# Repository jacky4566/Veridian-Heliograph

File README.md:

# Veridian-Heliograph
## What is it?
A hardy solar powered giver of GPS XYZ. Born from a need to always have a GPS device that can run for decades without any lithium batteries.
The Heliograph seeks to always provide a GPS Lat/Long position for the most severe travelers.
The whole device is cast in water clear epoxy, no ports, no holes, no batteries. Just a robust device that will provide a GPS position whenever outside.
A single M4 thread is provided for keychain or mounting on your favorite motorbike.

## Who wants it?
- Offshore Sailors
- Motorbikers
- Outdoorsmen
- Overlanders
- GNSS nerds

## Expected life
TBD

## Tech Features
- 2x 160mW solar panels
- TI nA Buck-Boost TPS63802
- 3.6V 70F Hybrid supercap
- UBlox Ultra low power M10 GPS processor
- STM32L432 MCU
- 3 Axis accelerometer with tap input, LIS3DH
- Sharp Sun readable Memory Display
- M4 screw thread for keychain or mounting

# Development and Details

## POWER SYSTEM
The power system comprises of 2 high efficiency solar panels at 120 degrees.  With this approach I hope the product design will always have access to some light to charge the super caps. Incoming power from the solar panels is feed through individual low drop shotcky diodes. With the diodes we loose ~200mV which is acceptable. 

The Supercaps are feed into Ti TPS63802 which provides buck-boost topography from the supercaps. Effectively allowing maximum use of the supercaps linear charge. 1.3 - 5.5V should be supported. Ti does also make an integrated BQ25570 MPPT with buck however I wanted to maximize the super caps voltage range.

VDD was selected at 3.0 volts as this was the minimum for the Sharp Memory LCD and the uBlox M10 GNSS chip. The M10 chip does also have a 1.8V version however we are still limited by the LCD. It might be possible to add a level converter however that quickly increases our BOM. The Buck-Boost seems like a good balance of low BOM and high efficiency.

## FIRMWARE
The firmware was written with the help of STM32CUBEIDE. The CubeIDE is pretty great for pre-generated code however some aspects can be hard to figure out for a novice. Since the BLE code could already be generated by the IDE most of my work was focused on the board level integration. Reading the sensors and putting that data into a nice GUI.
Firmware Features:
-	16MHz CPU speed coupled with 32.768kHz real time clock.
-	ADC 1Hz with DMA functionality to gather voltages. Supercap, temperature, and solar voltages.
-	SPI Display updating
-	GNSS processing using the Ublox PVT message. Less bytes to process compared to traditional NEMA messages. Super-e ultra low power tracking is set along side a software standby.
-	Accelerometer processing and Tap inputs

Some programming challenges I faced with my fight against CubeIDE:
-	Setting up the ADC DMA with proper callbacks. Some of the HAL calls need to be just right for the desired callbacks.
-	Learing about the SHARP display strange packet formatting. Data needs to be send as LSB.

## Housing
The Heliograph is essential without a housing. A basic model was 3D printed, then a reverse mold was made in rubber so the PCB and solar panels could be placed in a cavity and cast. Further development to come here.

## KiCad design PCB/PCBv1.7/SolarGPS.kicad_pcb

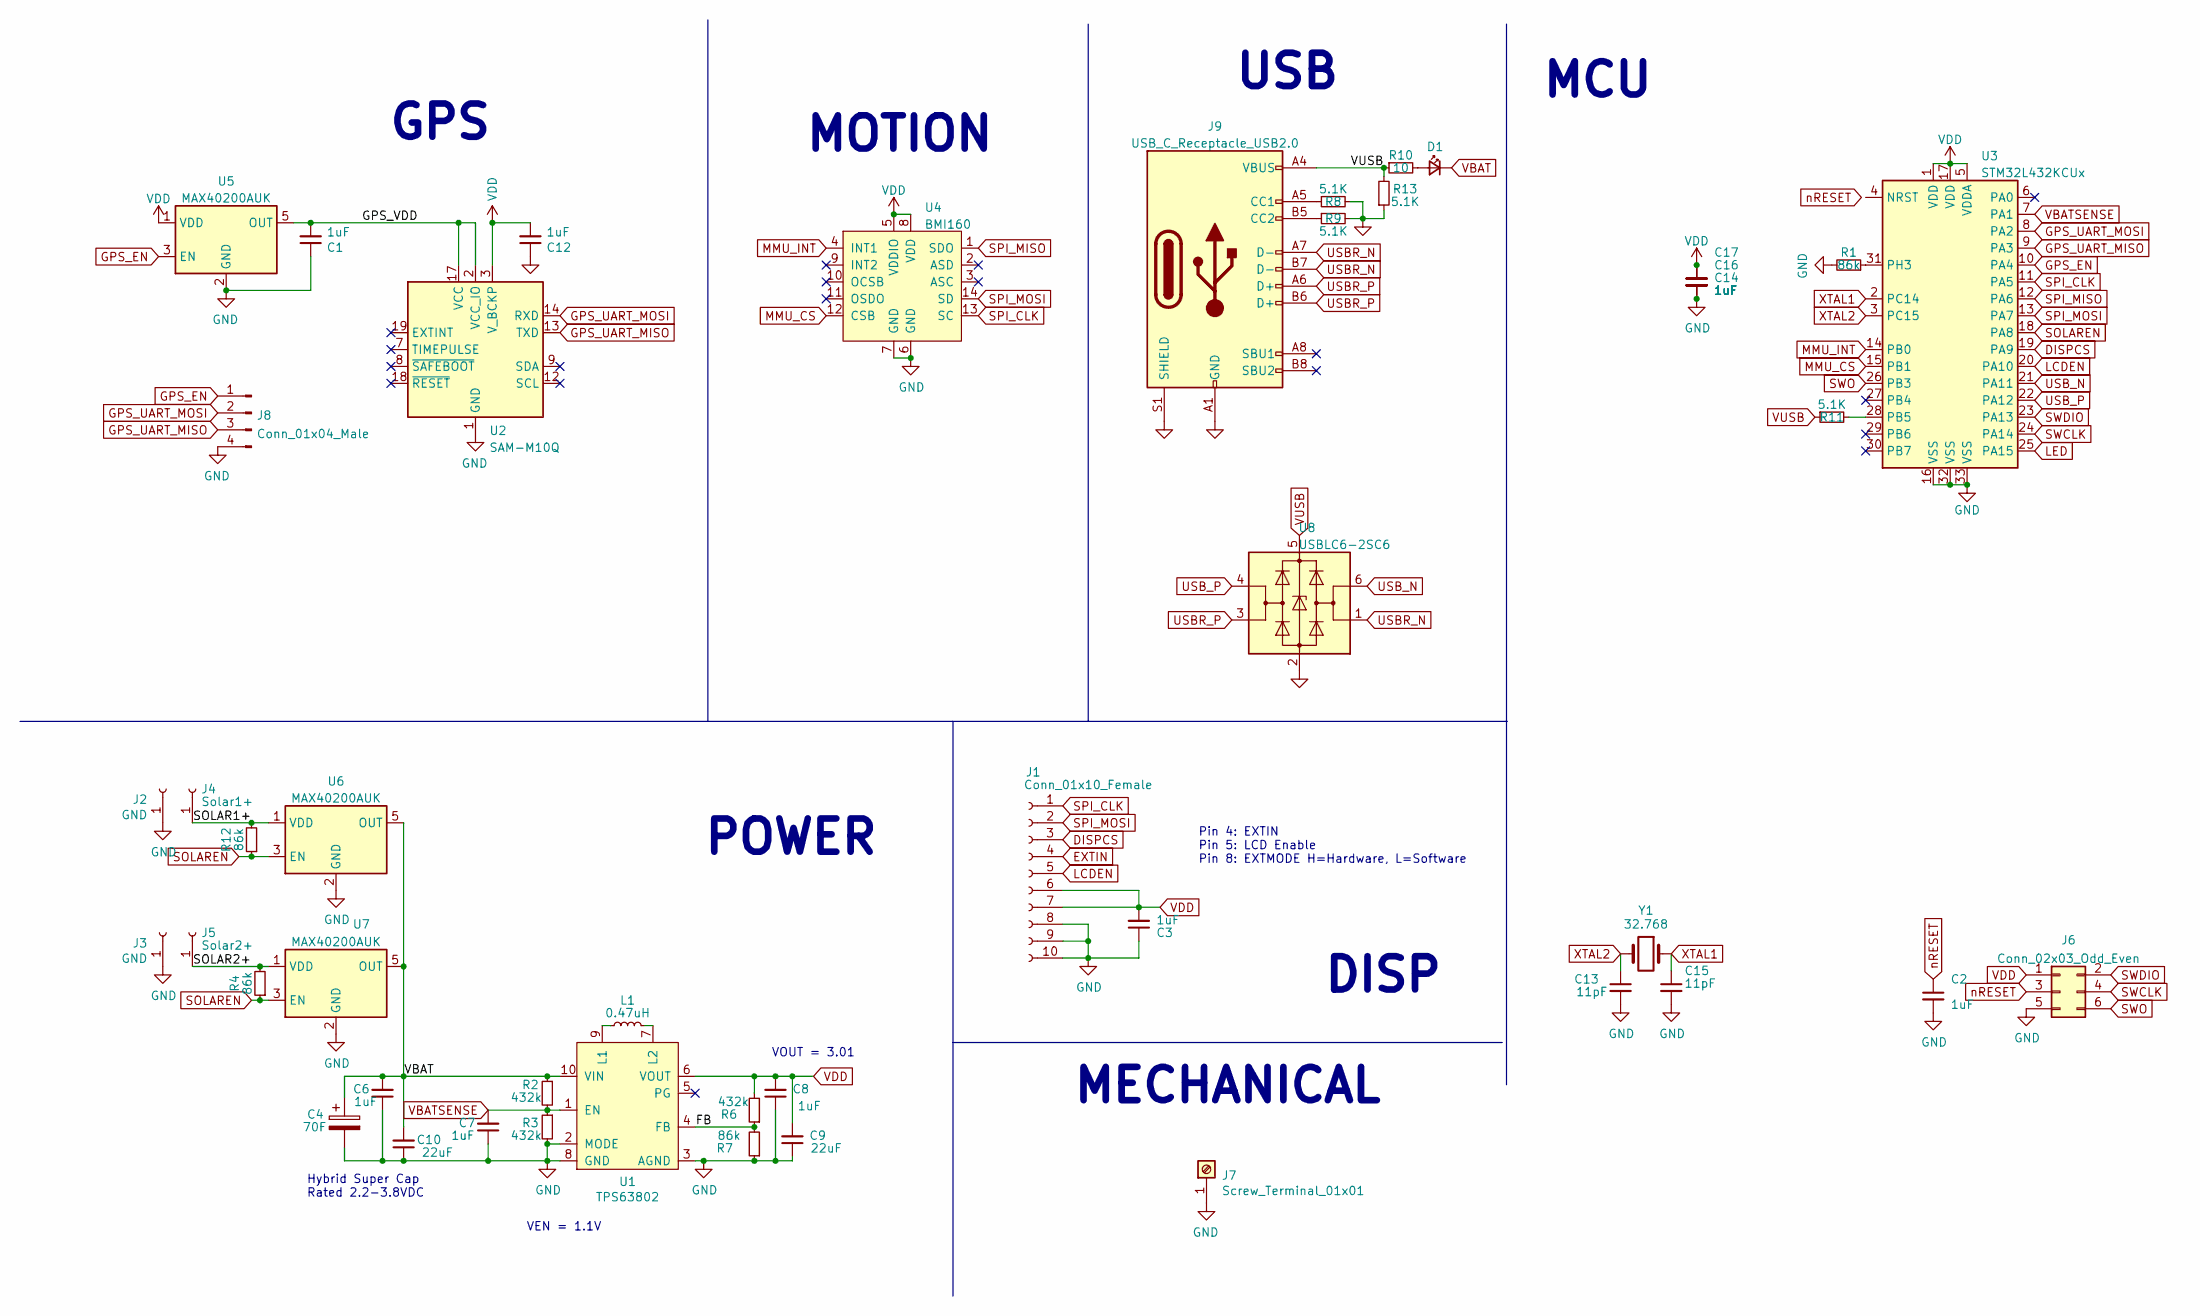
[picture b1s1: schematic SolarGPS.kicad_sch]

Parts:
C1, C2, C3, C6, C7, C8, C12, C14, C16, C17: 1uF; C_0603_1608Metric
C4: 70F; TPLC3R8-25MR8X20; Part TPLC3R8-25MR8X20
C9, C10: 22uF; C_1206_3216Metric
C13, C15: 11pF; C_0603_1608Metric
D1: LED_Small; D_0805_2012Metric
J1: Conn_01x10_Female; LS013B7DH03
J2, J3: GND; PinHeader_1x01_P2.54mm_Vertical
J4: Solar1+; PinHeader_1x01_P2.54mm_Vertical
J5: Solar2+; PinHeader_1x01_P2.54mm_Vertical
J6: Conn_02x03_Odd_Even; Tag-Connect_TC2030-IDC-NL_2x03_P1.27mm_Vertical
J7: Screw_Terminal_01x01; M4_RA_7792; Part 7792
J8: Conn_01x04_Male; PinSocket_1x04_P2.54mm_Vertical
J9: USB_C_Receptacle_USB2.0; USB_TYPE_C_PCB
L1: 0.47uH; L_0805_2012Metric_Pad1.15x1.40mm_HandSolder; Part DFE201612E
R1, R4, R7, R12: 86k; R_0603_1608Metric
R2, R3, R6: 432k; R_0603_1608Metric
R8, R9, R11, R13: 5.1K; R_0603_1608Metric
R10: 10; R_0805_2012Metric
U1: TPS63802; VREG_TPS63802DLAR
U2: SAM-M10Q; ublox_SAM-M8Q
U3: STM32L432KCUx; QFN-32-1EP_5x5mm_P0.5mm_EP3.45x3.45mm
U4: BMI160; MPN BMI160; Digi-Key_PN 828-1057-1-ND
U5, U6, U7: MAX40200AUK; SOT-23-5
U8: USBLC6-2SC6; SOT-23-6
Y1: 32.768; Crystal_SMD_3215-2Pin_3.2x1.5mm; Part SC32S-7PF20PPM

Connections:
/FB: R6.1, R7.2, U1.4 (FB)
/GPS_VDD: C1.2, U2.2 (VCC_IO), U2.17 (VCC), U5.5 (OUT)
/SOLAR1+: J4.1, R12.2, U6.1 (VDD)
/SOLAR2+: J5.1, R4.2, U7.1 (VDD)
DISPCS: J1.3, U3.19 (PA9)
EXTIN: J1.4
GND: C1.1, C2.2, C3.1, C4.2, C6.1, C7.1, C8.1, C9.1, C10.1, C12.1, C13.2, C14.2, C15.2, C16.2, C17.2, J1.8, J1.9, J1.10, J2.1, J3.1, J6.5, J7.1, J8.4, J9.A1 (GND), J9.A12 (GND), J9.B1 (GND), J9.B12 (GND), J9.S1 (SHIELD), R1.2, R3.2, R7.1, R8.2, R9.2, R13.1, U1.2 (MODE), U1.3 (AGND), U1.8 (GND), U2.1 (GND), U2.4 (GND), U2.5 (GND), U2.6 (GND), U2.10 (GND), U2.11 (GND), U2.15 (GND), U2.16 (GND), U2.20 (GND), U3.16 (VSS), U3.32 (VSS), U3.33 (VSS), U4.6 (GND), U4.7 (GND), U5.2 (GND), U6.2 (GND), U7.2 (GND), U8.2 (GND)
GPS_EN: J8.1, U3.10 (PA4), U5.3 (EN)
GPS_UART_MISO: J8.3, U2.13 (TXD), U3.9 (PA3)
GPS_UART_MOSI: J8.2, U2.14 (RXD), U3.8 (PA2)
LCDEN: J1.5, U3.20 (PA10)
LED: U3.25 (PA15)
MMU_CS: U3.15 (PB1), U4.12 (CSB)
MMU_INT: U3.14 (PB0), U4.4 (INT1)
unnamed: D1.2 (A), R10.2
unnamed: J9.A5 (CC1), R8.1
unnamed: J9.B5 (CC2), R9.1
unnamed: L1.1, U1.9 (L1)
unnamed: L1.2, U1.7 (L2)
unnamed: R1.1, U3.31 (PH3)
unnamed: R11.2, U3.28 (PB5)
SOLAREN: R4.1, R12.1, U3.18 (PA8), U6.3 (EN), U7.3 (EN)
SPI_CLK: J1.1, U3.11 (PA5), U4.13 (SC)
SPI_MISO: U3.12 (PA6), U4.1 (SDO)
SPI_MOSI: J1.2, U3.13 (PA7), U4.14 (SD)
SWCLK: J6.4, U3.24 (PA14)
SWDIO: J6.2, U3.23 (PA13)
SWO: J6.6, U3.26 (PB3)
USBR_N: J9.A7 (D-), J9.B7 (D-), U8.1 (I/O1)
USBR_P: J9.A6 (D+), J9.B6 (D+), U8.3 (I/O2)
USB_N: U3.21 (PA11), U8.6 (I/O1)
USB_P: U3.22 (PA12), U8.4 (I/O2)
VBAT: C4.1, C6.2, C10.2, D1.1 (K), R2.1, U1.10 (VIN), U6.5 (OUT), U7.5 (OUT)
VBATSENSE: C7.2, R2.2, R3.1, U1.1 (EN), U3.7 (PA1)
VDD: C3.2, C8.2, C9.2, C12.2, C14.1, C16.1, C17.1, J1.6, J1.7, J6.1, R6.2, U1.6 (VOUT), U2.3 (V_BCKP), U3.1 (VDD), U3.5 (VDDA), U3.17 (VDD), U4.5 (VDDIO), U4.8 (VDD), U5.1 (VDD)
VUSB: J9.A4 (VBUS), J9.A9 (VBUS), J9.B4 (VBUS), J9.B9 (VBUS), R10.1, R11.1, R13.2, U8.5 (VBUS)
XTAL1: C15.1, U3.2 (PC14), Y1.1
XTAL2: C13.1, U3.3 (PC15), Y1.2
nRESET: C2.1, J6.3

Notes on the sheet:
GPS
USB
MCU
Pin 4: EXTIN Pin 5: LCD Enable Pin 8: EXTMODE H=Hardware, L=Software
DISP
Hybrid Super Cap Rated 2.2-3.8VDC
VEN = 1.1V
POWER
VOUT = 3.01
MECHANICAL
MOTION

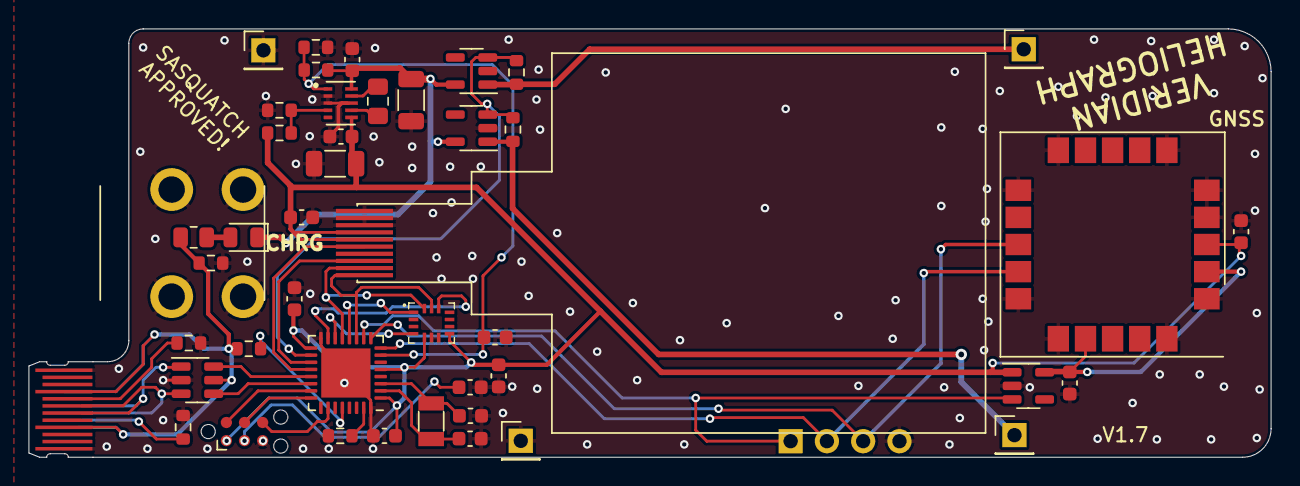
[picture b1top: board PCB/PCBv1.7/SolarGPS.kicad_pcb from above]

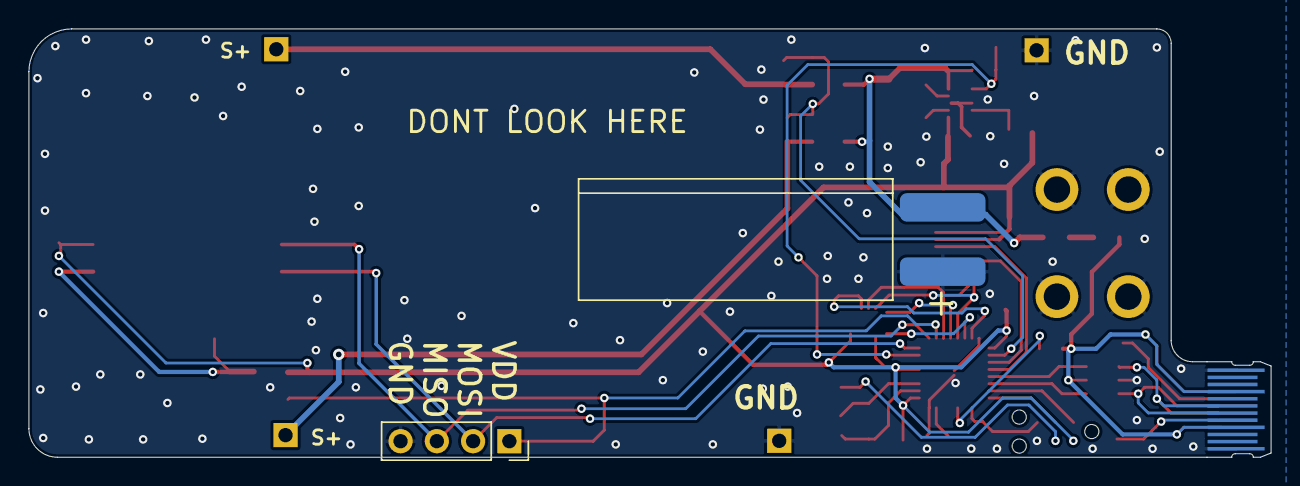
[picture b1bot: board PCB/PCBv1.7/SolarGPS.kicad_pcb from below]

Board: 2 copper layers, 87.0 x 30.0 mm, 47 parts (2 on the bottom side), 37 nets.

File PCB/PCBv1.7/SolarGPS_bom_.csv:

Component,Description,Part,References,Value,Footprint,Quantity Per PCB,Datasheet,Manufacture,Category,DK_Datasheet_Link,DK_Detail_Page,Digi-Key_PN,Family,MPN,Manufacturer,Status
1,"Unpolarized capacitor, small symbol",C_Small,C13 C15,11pF,C_0603_1608Metric,2,~,,,,,,,,,
2,"Unpolarized capacitor, small symbol",C_Small,C1 C2 C3 C6 C7 C8 C12 C14 C16 C17,1uF,C_0603_1608Metric,10,~,,,,,,,,,
3,"Unpolarized capacitor, small symbol",C_Small,C9 C10,22uF,C_1206_3216Metric,2,~,,,,,,,,,
4,Polarized capacitor,C_Polarized,C4,70F,TPLC3R8-25MR8X20,1,~,,,,,,,,,
5,"Light emitting diode, small symbol",LED_Small,D1,LED_Small,D_0805_2012Metric,1,~,,,,,,,,,
6,"Generic connector, single row, 01x04, script generated (kicad-library-utils/schlib/autogen/connector/)",Conn_01x04_Male,J8,Conn_01x04_Male,PinSocket_1x04_P2.54mm_Vertical,1,~,,,,,,,,,
7,"Generic connector, single row, 01x10, script generated (kicad-library-utils/schlib/autogen/connector/)",Conn_01x10_Female,J1,Conn_01x10_Female,LS013B7DH03,1,~,,,,,,,,,
8,"Generic connector, double row, 02x03, odd/even pin numbering scheme (row 1 odd numbers, row 2 even numbers), script generated (kicad-library-utils/schlib/autogen/connector/)",Conn_02x03_Odd_Even,J6,Conn_02x03_Odd_Even,Tag-Connect_TC2030-IDC-NL_2x03_P1.27mm_Vertical,1,~,,,,,,,,,
9,"Generic connector, single row, 01x01, script generated (kicad-library-utils/schlib/autogen/connector/)",Conn_01x01_Female,J2 J3 J4 J5,GND,PinHeader_1x01_P2.54mm_Vertical,4,~,,,,,,,,,
10,"Generic screw terminal, single row, 01x01, script generated (kicad-library-utils/schlib/autogen/connector/)",Screw_Terminal_01x01,J7,Screw_Terminal_01x01,M4_RA_7792,1,~,Keystone Electronics,,,,,,,,
11,USB 2.0-only Type-C Receptacle connector,USB_C_Receptacle_USB2.0,J9,USB_C_Receptacle_USB2.0,USB_TYPE_C_PCB,1,https://www.usb.org/sites/default/files/documents/usb_type-c.zip,,,,,,,,,
12,"Inductor, small symbol",L_Small,L1,0.47uH,L_0805_2012Metric_Pad1.15x1.40mm_HandSolder,1,~,,,,,,,,,
13,"Resistor, small symbol",R_Small,R10,10,R_0805_2012Metric,1,~,,,,,,,,,
14,"Resistor, small symbol",R_Small,R8 R9 R11 R13,5.1K,R_0603_1608Metric,4,~,,,,,,,,,
15,"Resistor, small symbol",R_Small,R1 R4 R7 R12,86.6k,R_0603_1608Metric,4,~,,,,,,,,,
16,"Resistor, small symbol",R_Small,R2 R3 R6,432k,R_0603_1608Metric,3,~,,,,,,,,,
17,IMU ACCEL/GYRO I2C/SPI 14LGA,BMI160,U4,BMI160,BMI160,1,https://ae-bst.resource.bosch.com/media/_tech/media/datashee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,,"Sensors, Transducers",https://ae-bst.resource.bosch.com/media/_tech/media/datashee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,/product-detail/en/bosch-sensortec/BMI160/828-1057-1-ND/6136308,828-1057-1-ND,Motion Sensors - IMUs (Inertial Measurement Units),BMI160,Bosch Sensortec,Active
18,"Ideal Diode, Ultra-Low Voltage Drop, 1.5-5.5V, 1A, SOT-23-5",MAX40200AUK,U5 U6 U7,MAX40200AUK,SOT-23-5,3,https://datasheets.maximintegrated.com/en/ds/MAX40200.pdf,,,,,,,,,
19,GPS ublox M8 variant,SAM-M8Q,U2,SAM-M10Q,ublox_SAM-M8Q,1,https://www.u-blox.com/sites/default/files/SAM-M8Q_DataSheet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,,,,,,,,,
20,"ARM Cortex-M4 MCU, 256KB flash, 64KB RAM, 80MHz, 1.71-3.6V, 26 GPIO, UFQFPN-32",STM32L432KCUx,U3,STM32L432KCUx,QFN-32-1EP_5x5mm_P0.5mm_EP3.45x3.45mm,1,http://www.st.com/st-web-ui/static/active/en/resource/techni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,,,,,,,,,
21,,TPS63802-VeridianDesigns,U1,TPS63802,VREG_TPS63802DLAR,1,,,,,,,,,,
22,"Very low capacitance ESD protection diode, 2 data-line, SOT-23-6",USBLC6-2SC6,U8,USBLC6-2SC6,SOT-23-6,1,https://www.st.com/resource/en/datasheet/usblc6-2.pdf,,,,,,,,,
23,Two pin crystal,Crystal,Y1,32.768,Crystal_SMD_3215-2Pin_3.2x1.5mm,1,~,,,,,,,,,





Component Groups:,23
Component Count:,47
Fitted Components:,47
Number of PCBs:,1
Total components:,47
Schematic Version:,
Schematic Date:,
PCB Variant:,default
BoM Date:,27-Apr-23 3:35:01 PM
Schematic Source:,SolarGPS.kicad_sch
KiCad Version:,Eeschema (6.0.10)

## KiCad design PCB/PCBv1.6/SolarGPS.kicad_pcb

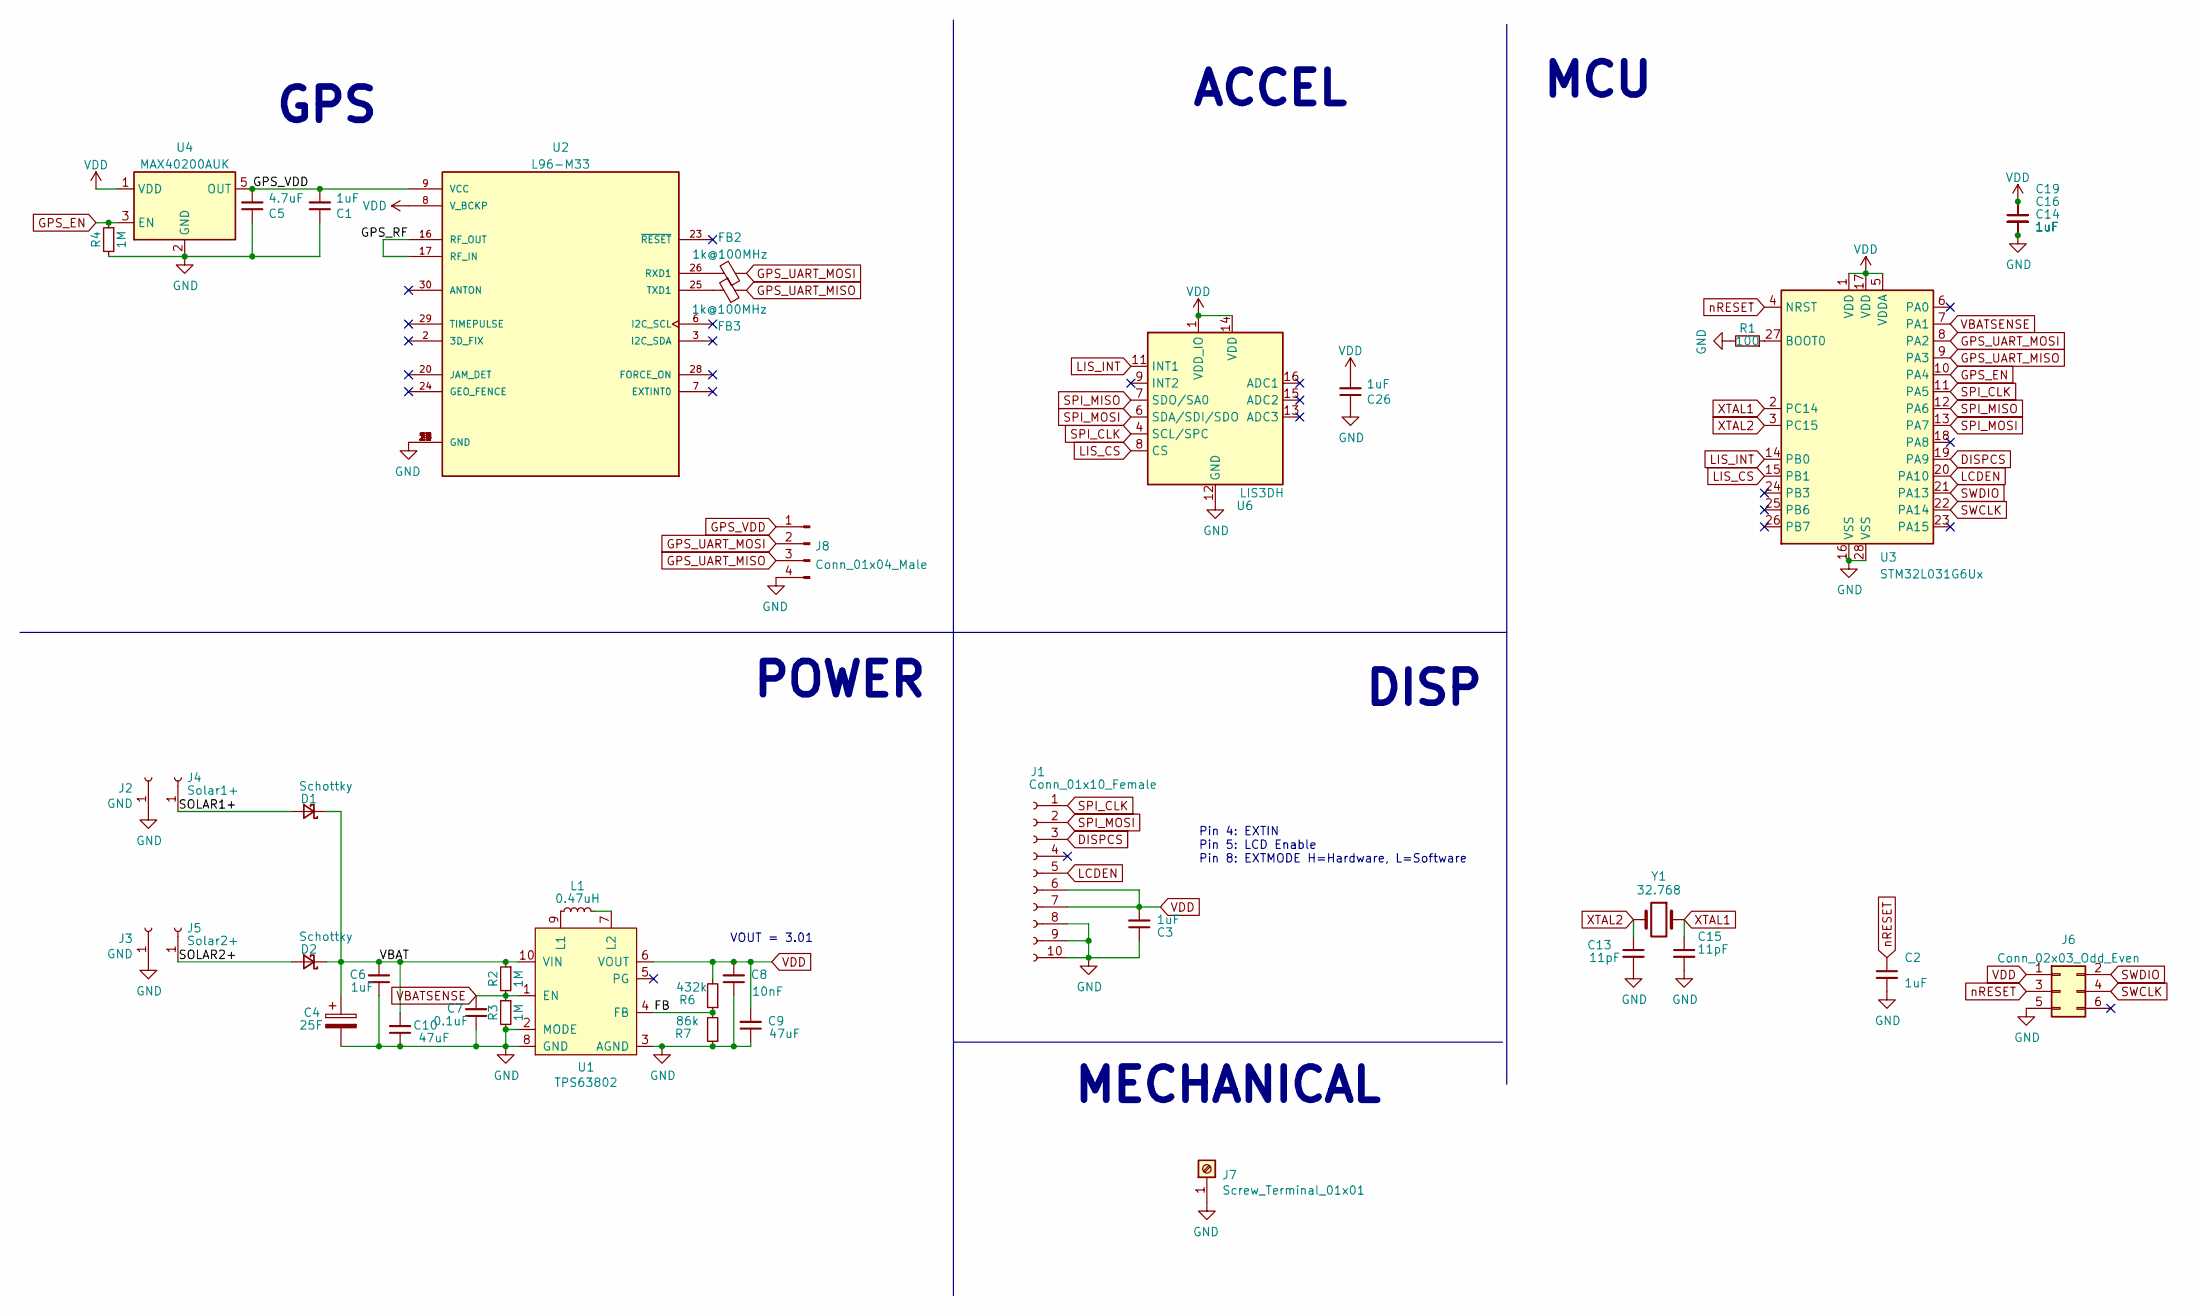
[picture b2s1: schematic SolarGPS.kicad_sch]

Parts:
C1, C2, C3, C6, C14, C16, C19, C26: 1uF; C_0603_1608Metric
C4: 25F; TPLC3R8-25MR8X20; Part TPLC3R8-25MR8X20
C5: 4.7uF; C_0805_2012Metric
C7: 0.1uF; C_0603_1608Metric
C8: 10nF; C_0603_1608Metric
C9, C10: 47uF; C_1206_3216Metric
C13, C15: 11pF; C_0603_1608Metric
D1, D2: Schottky; D_SOD-323_HandSoldering; Part B0530WS
FB2, FB3: 1k@100MHz; R_0603_1608Metric
J1: Conn_01x10_Female; LS013B7DH03
J2, J3: GND; PinHeader_1x01_P2.54mm_Vertical
J4: Solar1+; PinHeader_1x01_P2.54mm_Vertical
J5: Solar2+; PinHeader_1x01_P2.54mm_Vertical
J6: Conn_02x03_Odd_Even; Tag-Connect_TC2030-IDC-NL_2x03_P1.27mm_Vertical
J7: Screw_Terminal_01x01; M4_RA_7792; Part 7792
J8: Conn_01x04_Male; PinSocket_1x04_P2.54mm_Vertical
L1: 0.47uH; L_0805_2012Metric_Pad1.05x1.20mm_HandSolder; Part DFE201612E
R1: 100; R_0603_1608Metric
R2, R3, R4: 1M; R_0603_1608Metric
R6: 432k; R_0603_1608Metric
R7: 86k; R_0603_1608Metric
U1: TPS63802; VREG_TPS63802DLAR
U2: L96-M33; XCVR_L96-M33
U3: STM32L031G6Ux; QFN-28_4x4mm_P0.5mm
U4: MAX40200AUK; SOT-23-5
U6: LIS3DH; LGA-16_3x3mm_P0.5mm_LayoutBorder3x5y
Y1: 32.768; Crystal_SMD_3215-2Pin_3.2x1.5mm; Part SC32S-7PF20PPM

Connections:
/FB: R6.1, R7.2, U1.4 (FB)
/GPS_RF: U2.16 (RF_OUT), U2.17 (RF_IN)
/SOLAR1+: D1.2 (A), J4.1
/SOLAR2+: D2.2 (A), J5.1
/VBAT: C4.1, C6.2, C10.2, D1.1 (K), D2.1 (K), R2.1, U1.10 (VIN)
DISPCS: J1.3, U3.19 (PA9)
GND: C1.1, C2.2, C3.1, C4.2, C5.1, C6.1, C7.1, C8.1, C9.1, C10.1, C13.2, C14.2, C15.2, C16.2, C19.2, C26.1, J1.8, J1.9, J1.10, J2.1, J3.1, J6.5, J7.1, J8.4, R1.2, R3.2, R4.2, R7.1, U1.2 (MODE), U1.3 (AGND), U1.8 (GND), U2.4 (GND), U2.5 (GND), U2.10 (GND), U2.11 (GND), U2.12 (GND), U2.13 (GND), U2.14 (GND), U2.15 (GND), U2.18 (GND), U2.19 (GND), U2.21 (GND), U2.22 (GND), U2.27 (GND), U2.31 (GND), U3.16 (VSS), U3.28 (VSS), U4.2 (GND), U6.5 (GND), U6.10 (GND), U6.12 (GND)
GPS_EN: R4.1, U3.10 (PA4), U4.3 (EN)
GPS_UART_MISO: FB3.2, J8.3, U3.9 (PA3)
GPS_UART_MOSI: FB2.1, J8.2, U3.8 (PA2)
GPS_VDD: C1.2, C5.2, J8.1, U2.9 (VCC), U4.5 (OUT)
LCDEN: J1.5, U3.20 (PA10)
LIS_CS: U3.15 (PB1), U6.8 (CS)
LIS_INT: U3.14 (PB0), U6.11 (INT1)
unnamed: FB2.2, U2.26 (RXD1)
unnamed: FB3.1, U2.25 (TXD1)
unnamed: L1.1, U1.9 (L1)
unnamed: L1.2, U1.7 (L2)
unnamed: R1.1, U3.27 (BOOT0)
SPI_CLK: J1.1, U3.11 (PA5), U6.4 (SCL/SPC)
SPI_MISO: U3.12 (PA6), U6.7 (SDO/SA0)
SPI_MOSI: J1.2, U3.13 (PA7), U6.6 (SDA/SDI/SDO)
SWCLK: J6.4, U3.22 (PA14)
SWDIO: J6.2, U3.21 (PA13)
VBATSENSE: C7.2, R2.2, R3.1, U1.1 (EN), U3.7 (PA1)
VDD: C3.2, C8.2, C9.2, C14.1, C16.1, C19.1, C26.2, J1.6, J1.7, J6.1, R6.2, U1.6 (VOUT), U2.8 (V_BCKP), U3.1 (VDD), U3.5 (VDDA), U3.17 (VDD), U4.1 (VDD), U6.1 (VDD_IO), U6.14 (VDD)
XTAL1: C15.1, U3.2 (PC14), Y1.1
XTAL2: C13.1, U3.3 (PC15), Y1.2
nRESET: C2.1, J6.3, U3.4 (NRST)

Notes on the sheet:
GPS
MCU
ACCEL
Pin 4: EXTIN Pin 5: LCD Enable Pin 8: EXTMODE H=Hardware, L=Software
DISP
POWER
VOUT = 3.01
MECHANICAL

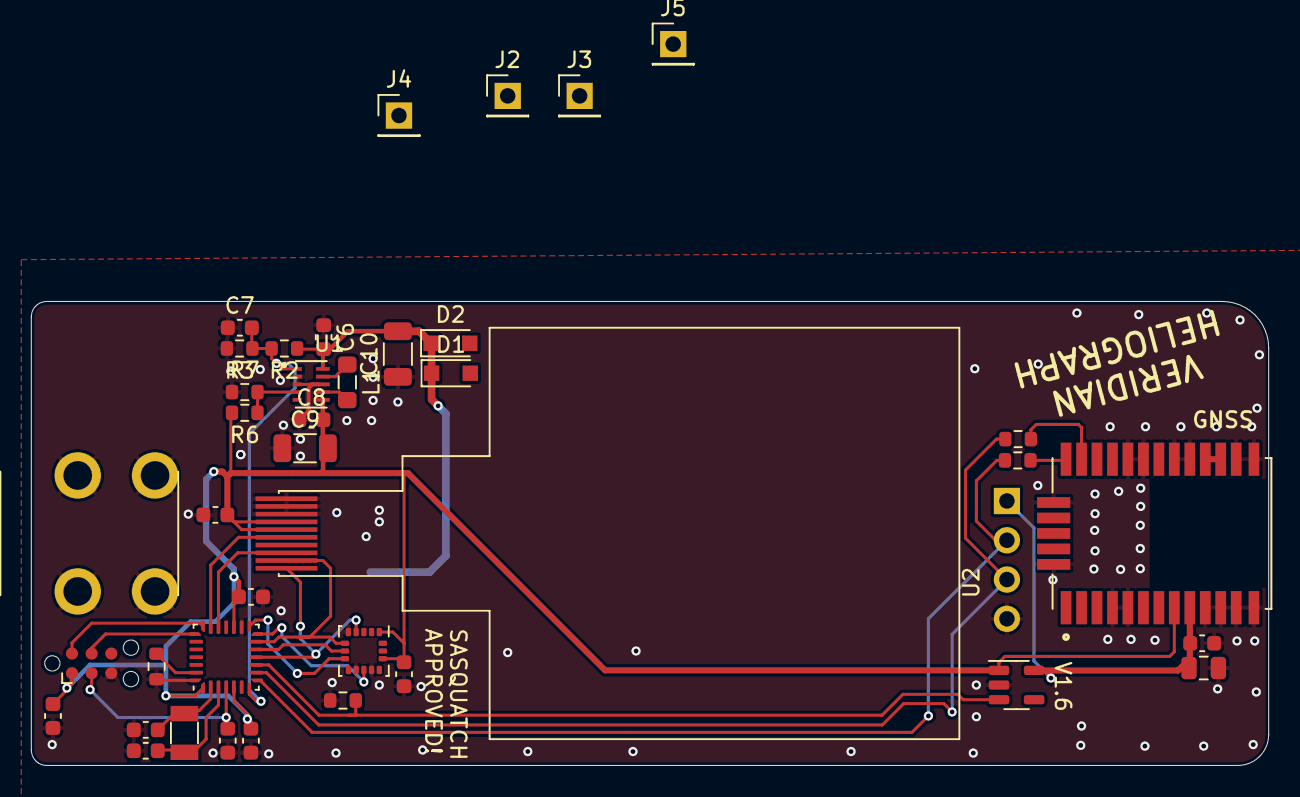
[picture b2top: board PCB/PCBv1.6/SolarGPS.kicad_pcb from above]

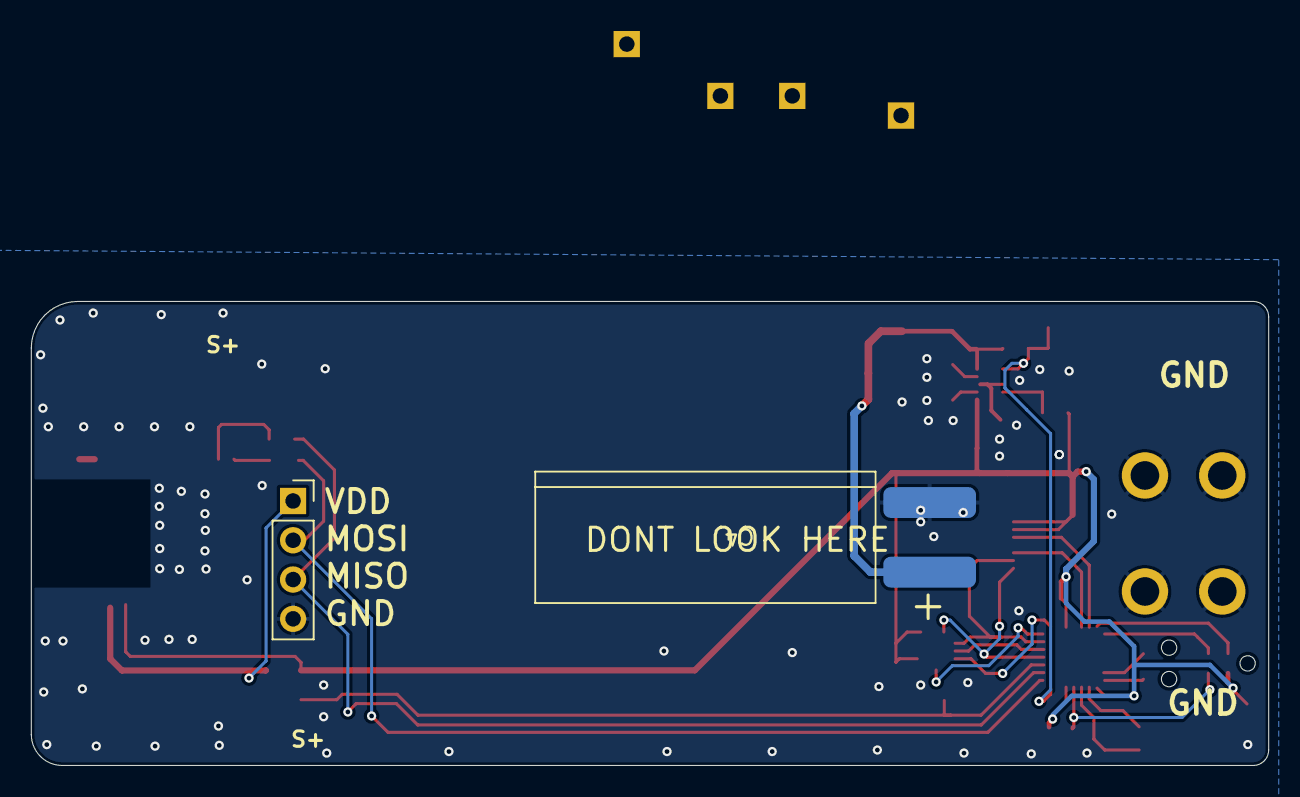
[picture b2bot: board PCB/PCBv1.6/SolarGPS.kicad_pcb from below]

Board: 2 copper layers, 80.0 x 30.0 mm, 41 parts (2 on the bottom side), 29 nets.

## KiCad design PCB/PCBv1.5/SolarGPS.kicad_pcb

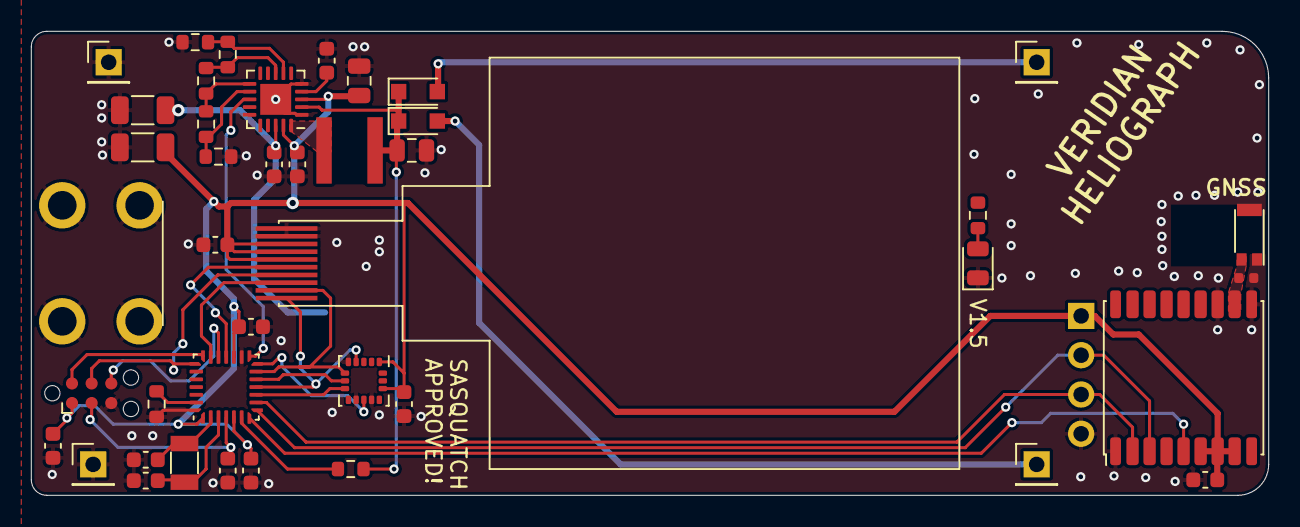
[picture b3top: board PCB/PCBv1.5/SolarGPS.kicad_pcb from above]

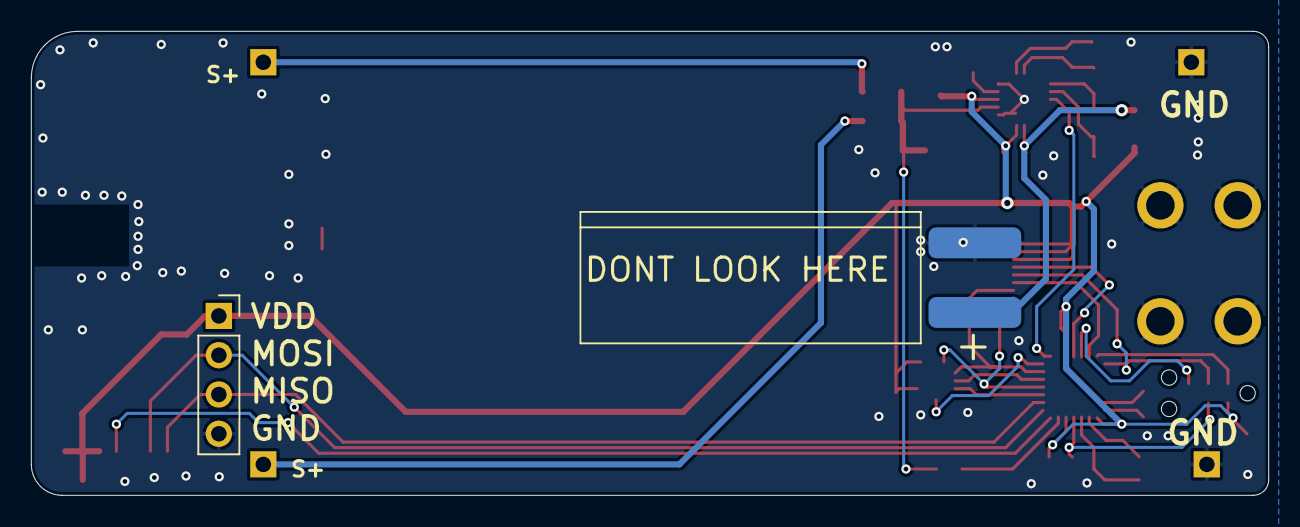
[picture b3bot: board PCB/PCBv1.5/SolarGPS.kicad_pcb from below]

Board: 2 copper layers, 80.0 x 30.0 mm, 44 parts (2 on the bottom side), 33 nets.

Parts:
AE1: Antenna_Shield; Pulse_W3011
C1: 3.3pF; C_0402_1005Metric
C2, C3, C5, C14, C16, C19, C26: 1uF; C_0603_1608Metric
C4, C11: 4.7uF; C_0805_2012Metric
C6, C7, C9: 10nF; C_0603_1608Metric
C8: 25F; TPLC3R8-25MR8X20
C10, C12: 47uF; C_1206_3216Metric
C13, C15: 11pF; C_0603_1608Metric
D1, D3: Schottky; D_SOD-323_HandSoldering
D2: LED; D_0805_2012Metric
J1: Conn_01x10_Female; LS013B7DH03
J2: Solar2+; PinHeader_1x01_P2.54mm_Vertical
J3: Solar1+; PinHeader_1x01_P2.54mm_Vertical
J4, J5: GND; PinHeader_1x01_P2.54mm_Vertical
J6: Conn_02x03_Odd_Even; Tag-Connect_TC2030-IDC-NL_2x03_P1.27mm_Vertical
J7: Screw_Terminal_01x01; M4_RA_7792
J8: Conn_01x04_Male; PinSocket_1x04_P2.54mm_Vertical
L1: 22uH; 744031220
R1, R2, R3: 100; R_0603_1608Metric
ROK1: 6.49M; R_0603_1608Metric
ROK2: 5.36M; R_0603_1608Metric
ROK3: 1M; R_0603_1608Metric
ROV1, ROV2: 6.49M; R_0603_1608Metric
U1: BQ25505; QFN-20-1EP_3.5x3.5mm_P0.5mm_EP2x2mm
U2: MAX-M10Q; ublox_MAX
U3: STM32L031G6Ux; QFN-28_4x4mm_P0.5mm
U6: LIS3DH; LGA-16_3x3mm_P0.5mm_LayoutBorder3x5y
Y1: 32.768; Crystal_SMD_3215-2Pin_3.2x1.5mm

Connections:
/GPS_RF: AE1.1 (A), C1.2, U2.11 (RF_IN)
/LBOOST: L1.2, U1.20 (LBOOST)
/VRDIV: ROK3.1, ROV2.1, U1.8 (VRDIV)
DISPCS: J1.3, U3.20 (PA10)
DISPEN: J1.5, U3.18 (PA8)
EXTCOMIN: J1.4, J6.4, U3.22 (PA14)
GND: AE1.2 (Shield), C1.1, C2.2, C3.1, C4.2, C5.1, C6.2, C7.1, C8.2, C9.1, C10.1, C11.1, C12.1, C13.2, C14.2, C15.2, C16.2, C19.2, C26.1, D2.1 (K), J1.9, J1.10, J4.1, J5.1, J6.5, J7.1, J8.4, R1.2, ROK1.2, ROV1.2, U1.1 (VSS), U1.5 (EN), U1.15 (VSS), U1.21 (VSS), U2.1 (GND), U2.10 (GND), U2.12 (GND), U3.16 (VSS), U3.28 (VSS), U6.5 (GND), U6.10 (GND), U6.12 (GND)
GPS_EXINT: U2.5 (EXTINT), U3.7 (PA1)
GPS_UART_MISO: J8.3, U2.2 (TXD), U3.9 (PA3)
GPS_UART_MOSI: J8.2, U2.3 (RXD), U3.8 (PA2)
LIS_CS: U3.10 (PA4), U6.8 (CS)
LIS_INT: U3.14 (PB0), U6.11 (INT1)
unnamed: C6.1, U1.4 (VREF_SAMP)
unnamed: D1.2 (A), J2.1
unnamed: D2.2 (A), R2.1
unnamed: D3.2 (A), J3.1
unnamed: R1.1, U3.27 (BOOT0)
unnamed: R3.1, U3.6 (PA0)
unnamed: ROK1.1, ROK2.2, U1.12 (OK_PROG)
unnamed: ROK2.1, ROK3.2, U1.11 (OK_HYST)
unnamed: ROV1.1, ROV2.2, U1.7 (VBAT_OV)
SOLAR+: C4.1, D1.1 (K), D3.1 (K), L1.1, R3.2, U1.2 (VIN_DC)
SPI_CLK: J1.1, U3.11 (PA5), U6.4 (SCL/SPC)
SPI_MISO: U3.12 (PA6), U6.7 (SDO/SA0)
SPI_MOSI: J1.2, U3.13 (PA7), U6.6 (SDA/SDI/SDO)
SWDIO: J6.2, U3.21 (PA13)
SWO: J6.6, U3.19 (PA9)
VBAT: C8.1, C9.2, C10.2, U1.18 (VBAT_SEC)
VBAT_OK: U1.13 (VBAT_OK), U3.15 (PB1)
VDD: C3.2, C5.2, C7.2, C11.2, C12.2, C14.1, C16.1, C19.1, C26.2, J1.6, J1.7, J1.8, J6.1, J8.1, U1.3 (VOC_SAMP), U1.19 (VSTOR), U2.6 (V_BCKP), U2.7 (VCC_IO), U2.8 (VCC), U3.1 (VDD), U3.5 (VDDA), U3.17 (VDD), U6.1 (VDD_IO), U6.14 (VDD)
XTAL1: C15.1, U3.2 (PC14), Y1.1
XTAL2: C13.1, U3.3 (PC15), Y1.2
nRESET: C2.1, J6.3, U3.4 (NRST)

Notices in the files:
Firmware/STM32IDE/Heliograph_L432/Core/Src/main.c:
Copyright (c) 2023 STMicroelectronics.
All rights reserved.
This software is licensed under terms that can be found in the LICENSE file
